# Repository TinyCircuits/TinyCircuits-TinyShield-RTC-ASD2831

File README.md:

# TinyCircuits TinyShield RTC Board
# ASD2831 Rev4

The design files are located under design-files/ for the TinyCircuits ASD2831 Rev 4 PCB.  This is a TinyShield board (20mm x 20mm) that has a Real-time clock.

Format is in Cadsoft Eagle format - Eagle version 6.2 was used for the original design.

For more infomation on this, check out the product page at TinyCircuits.com:  https://tinycircuits.com/collections/sensors/products/real-time-clock-tinyshield

# License:

Design by TinyCircuits.
All design files are released under the Creative Commons Attribution Share-Alike 3.0 License, see the following link for details: http://creativecommons.org/licenses/by-sa/3.0

All text above must be included in any redistribution or derived design

This project uses designs and concepts developed as part of the Arduino project and the LilyPad project.  The TinyCircuits design files themselves (schematics, PCB and libraries) are not directly derived from these works' design files and have been created new, however the concepts and basic architecture behind the TinyDuino and TinyLily products are derived and we thank the hard work of the organizations below for their contributions to open-source hardware:
  
Original Arduino Uno Design by Team Arduino

LilyPad Arduino Design by Leah Buechley and Sparkfun Electronics

Please support the open-source hardware community

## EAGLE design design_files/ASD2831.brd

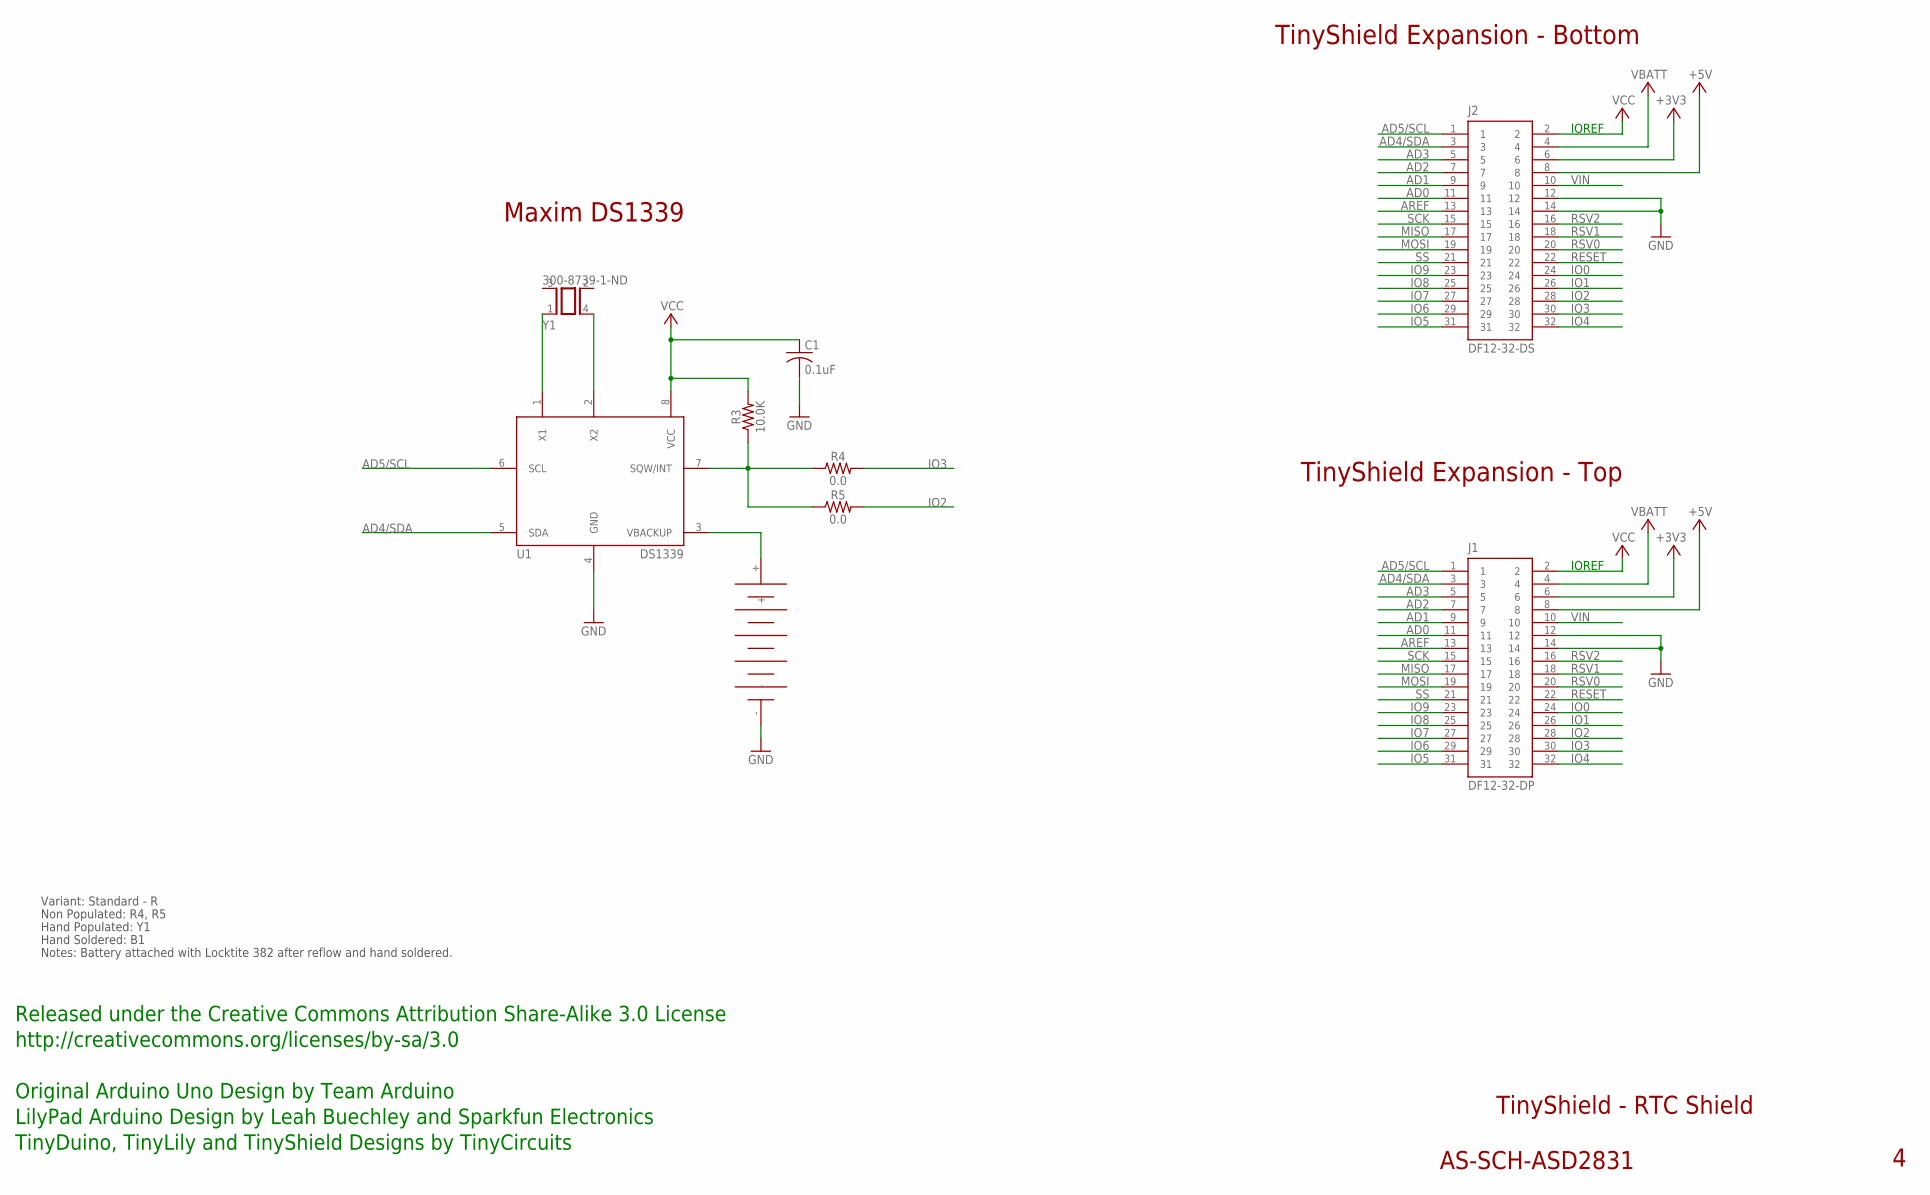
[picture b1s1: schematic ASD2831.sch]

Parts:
B1: ML-920S/DN
C1: 0.1uF; C0402
J1: DF12-32-DP; PARTNO AS-ITM-00015
J2: DF12-32-DS; PARTNO AS-ITM-00012
R3: 10.0K; 0402; PARTNO AS-ITM-00032
R4: 0.0; 0402_SHORT
R5: 0.0; 0402
U1: DS1339; 8-USOP
Y1: 300-8739-1-ND; CM200C-32.768KDZBT

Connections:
+3V3: J1.6, J2.6
+5V: J1.8, J2.8
AD0: J1.11, J2.11
AD1: J1.9, J2.9
AD2: J1.7, J2.7
AD3: J1.5, J2.5
AD4/SDA: J1.3, J2.3, U1.5 (SDA)
AD5/SCL: J1.1, J2.1, U1.6 (SCL)
AREF: J1.13, J2.13
GND: B1.-, C1.2, J1.12, J1.14, J2.12, J2.14, U1.4 (GND)
IO0: J1.24, J2.24
IO1: J1.26, J2.26
IO2: J1.28, J2.28, R5.2
IO3: J1.30, J2.30, R4.2
IO4: J1.32, J2.32
IO5: J1.31, J2.31
IO6: J1.29, J2.29
IO7: J1.27, J2.27
IO8: J1.25, J2.25
IO9: J1.23, J2.23
MISO: J1.17, J2.17
MOSI: J1.19, J2.19
unnamed: U1.1 (X1), Y1.1
unnamed: U1.2 (X2), Y1.4 (2)
unnamed: R3.1, R4.1, R5.1, U1.7 (SQW/INT)
unnamed: B1.+, U1.3 (VBACKUP)
RESET: J1.22, J2.22
RSV0: J1.20, J2.20
RSV1: J1.18, J2.18
RSV2: J1.16, J2.16
SCK: J1.15, J2.15
SS: J1.21, J2.21
VBATT: J1.4, J2.4
VCC: C1.1, J1.2, J2.2, R3.2, U1.8 (VCC)
VIN: J1.10, J2.10

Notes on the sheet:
TinyShield Expansion - Bottom
TinyShield - RTC Shield
AS-SCH-ASD2831
TinyShield Expansion - Top
IOREF
Released under the Creative Commons Attribution Share-Alike 3.0 License
http://creativecommons.org/licenses/by-sa/3.0
LilyPad Arduino Design by Leah Buechley and Sparkfun Electronics
TinyDuino, TinyLily and TinyShield Designs by TinyCircuits
Original Arduino Uno Design by Team Arduino
Maxim DS1339
Non Populated: R4, R5
Hand Populated: Y1
Hand Soldered: B1
Notes: Battery attached with Locktite 382 after reflow and hand soldered.
Variant: Standard - R

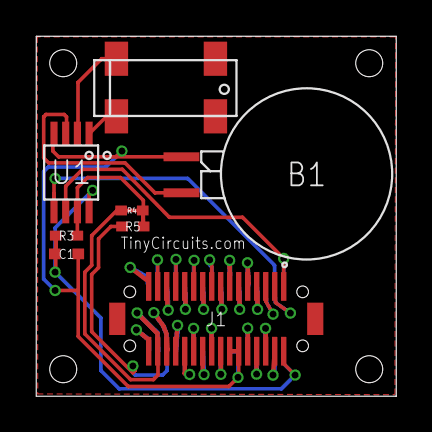
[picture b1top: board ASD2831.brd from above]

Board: 2 copper layers, 20.0 x 20.0 mm, 10 parts (1 on the bottom side), 35 nets.

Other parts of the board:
U$1: DOCFIELD-TINYCIRCUITS-PCB

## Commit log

2019-01-02 update format
2019-05-22 made new code
2019-05-22 added library files
2019-05-22 added images
2019-05-22 added .zip file
2019-05-22 added library .zip files
2019-05-23 updated images
2019-05-28 fixed spelling
2019-05-28 added libraries to example code directory
2020-02-11 image update
2020-07-28 Add CAD data
2020-08-14 Update CAD drawing
